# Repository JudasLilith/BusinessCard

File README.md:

# Business Card Framework

A place for people to get started on making their own PCB business card!

Design originally from: https://jams.hackclub.com/jam/hacker-card

find some logos to place, or use the materials list to start new!

## Bill of materials:
(All parts are sourced from the original guide, but here's a comprehensive list)

- A antenna

- A NT3H2111W0FHKH NFC Chip

- 220nF capacitors 

- 2296C 2v LEDs

- numerous logos

## Logos Included:

These are some Logos I added inside, but please acknowledge that I had to manually add a few lines when the imports for kicad was botched & the logos might look a bit different than expected.
(All of the logos are in the nfcactual.pretty folder)

- Onshape

- Inventor

- Fusion 360

- KiCad

- Solidworks

- Godot

- Raspberry Pi

- Klipper

- JLCPCB

- Davinci Resolve

- Darktable

- WPILib

- ArchLinux

- Hyprland

- Debian

- FRC team 624

- Unity

- Hack Club

- NHRL

- FIRST Robotics Competition

Each logo has a length of 1 cm, exept for debian and Godot!

 **Any additional Logos you want/want me to add, put them an issue and I'll update it!**

## where can I make my QR code?

!

-You can make it by pasting on this website: https://www.qr-code-generator.com/

**DISCLAIMER:** I haven't tried importing this myself, so use at your own risk!

#alternative method
-Make a new footprint with create footprint
-pick qr code wizard
in the slots that says string value and put your URL inisde the sheet.

Personally, I recommend writing a link to your personal github
Or you can make your own website and link it to the qr code

**DISCLAMER** For beginners like me, I really wasn't able to find a way to scale the QR code to the wanted dimensions, so you might not be able to do it!

Have fun building!
Any additions that might look good, you can add an issues for it and I'll review it!

### After obtaining from JLCPCB:
* Using [NFC Tools](https://nfc.software/), flash this command to initialize the NFC from factory settings:

A2:03:E1:10:6D:00,A2:04:03:04:D8:00,A2:05:00:00:FE:00

* Go to Other > Advanced NFC commands > I understand >

**p.s:** 
* make sure to draw the outlines, or else they look pretty janky.
* Be sure to check the **<u>polarity on the capacitors, LED, and the orientation on the NFC Chip;</u>** they are a lot smaller than you expect it & might have a hard time fixing it!

## Have fun making!

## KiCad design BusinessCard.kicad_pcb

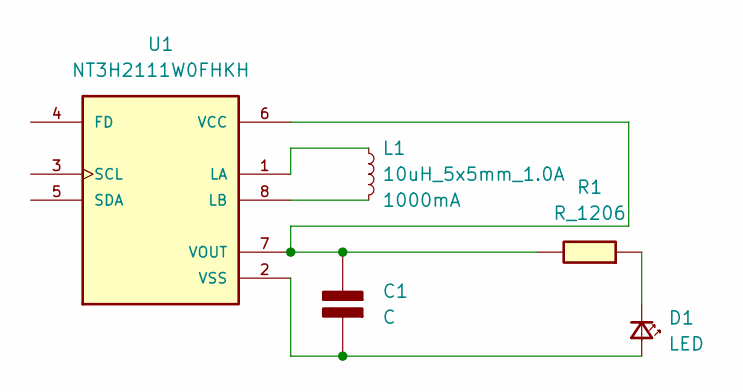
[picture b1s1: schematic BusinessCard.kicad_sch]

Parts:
C1: C; CAPC1608X90N; Rating V
D1: LED; LED0805-R-RD
L1: 10uH_5x5mm_1.0A; 25X48MM_NFC_ANTENNA
R1: R_1206; C0603
U1: NT3H2111W0FHKH; QFN8P50_160X160X50L40X20N

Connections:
unnamed: C1.1 (+), D1.2 (A), U1.2 (VSS)
unnamed: C1.2 (-), R1.1, U1.6 (VCC), U1.7 (VOUT)
unnamed: D1.1 (K), R1.2
unnamed: L1.1, U1.1 (LA)
unnamed: L1.2, U1.8 (LB)

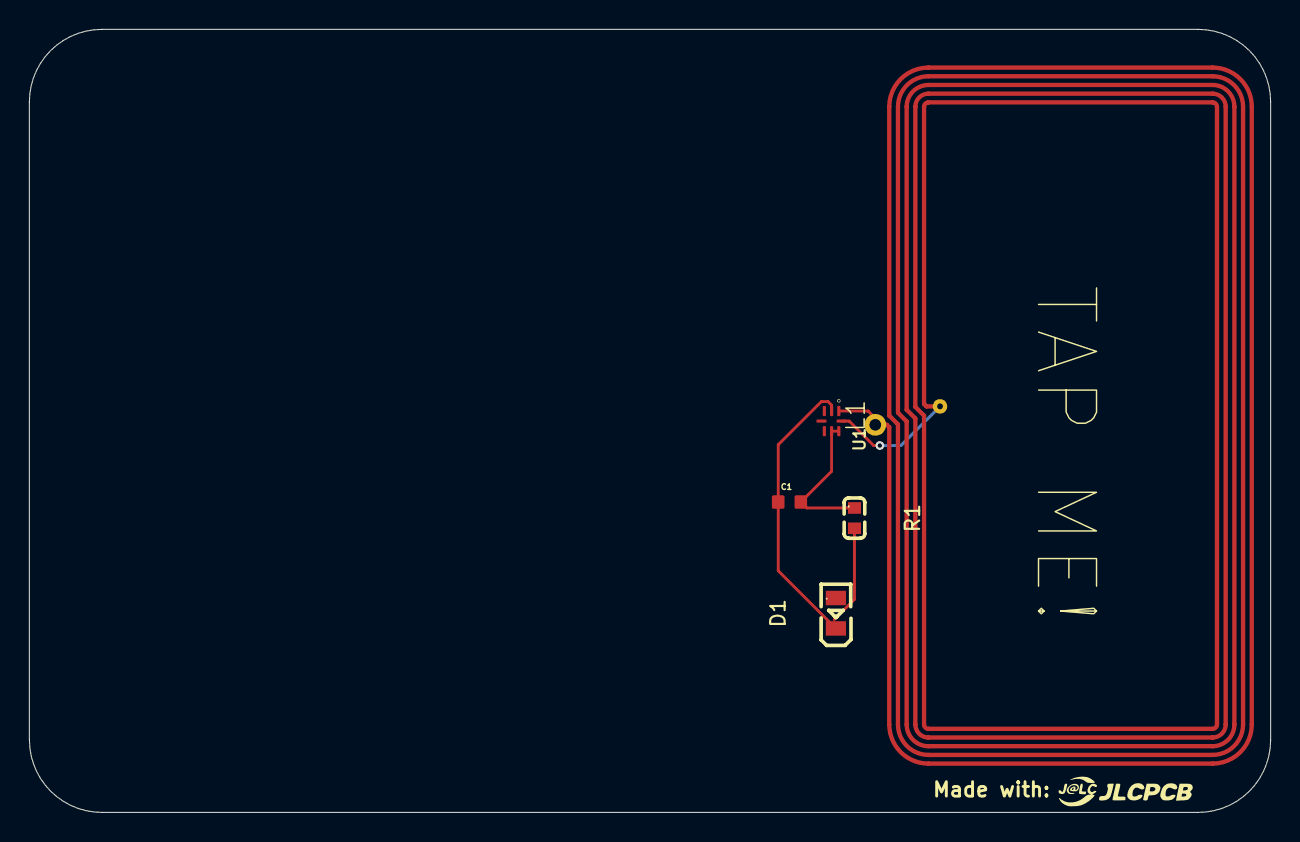
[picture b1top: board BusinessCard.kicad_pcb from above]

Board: 2 copper layers, 85.6 x 54.0 mm, 5 parts (0 on the bottom side), 5 nets.

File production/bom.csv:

Designator,Footprint,Quantity,Value,LCSC Part #
C1,CP_Elec_5x5.3,1,C,
D1,0603,1,LED,
L1,25X48MM_NFC_ANTENNA,1,10uH_5x5mm_1.0A,
R1,R_1206,1,47,
U1,QFN8P50_160X160X50L40X20N,1,NT3H2111W0FHKH,

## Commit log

2026-02-01 First start, added the schematic and a few logos to use
2026-02-04 logos added to footprint
2026-02-04 Add initial content to README.md
2026-02-04 new footprints, got the pads working
2026-02-07 Made a few design changes, started the intro
2026-02-07 easfd
2026-02-10 Final push after ordering
2026-02-10 minor tweaks on readme
2026-02-11 A sub-project where I make a business card for a company I'm working for
2026-02-15 made a new card on a new branch for a company(custom job)
2026-02-16 Update README with logo size and NFC setup instructions
    Added notes about logo sizes and NFC initialization steps.
2026-02-17 final updates
2026-06-01 final update
